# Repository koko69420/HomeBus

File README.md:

<h1 align="center">HomeBus</h1>

<p align="center">
  <strong>A deterministic, hard-wired distributed home automation platform built on 32-bit RISC-V microcontrollers, full-duplex RS-422 differential networking, centralized 24V DC power distribution, and native Home Assistant integration.</strong>
</p>

<p align="center">
  <a href="#system-architecture">Architecture</a> •
  <a href="#hierarchical-documentation">Documentation Map</a> •
  <a href="#hardware-overview">Hardware</a> •
  <a href="#protocol--firmware">Protocol & Firmware</a> •
  <a href="#repository-structure">Repository Structure</a> •
  <a href="#getting-started--toolchain">Getting Started</a>
</p>

---

## Overview & Motivation

Modern smart homes face severe reliability degradation when relying on congested 2.4 GHz wireless networks (Wi-Fi, Zigbee, Bluetooth). RF interference, wireless mesh packet dropouts, battery maintenance for wall sensors, and high-latency cloud dependencies undermine home automation dependability.

**HomeBus** solves this by delivering an industrial-grade, hard-wired residential infrastructure:
- **Full-Duplex RS-422 Differential Signaling**: Non-blocking serial communications operating at high baud rates without bus collision arbitration.
- **Centralized 24V DC Power Distribution**: Power and high-speed data are distributed over a single multi-conductor cable (CAT5e), eliminating failure-prone miniature AC-DC supplies inside cramped wall flush boxes.
- **Hardware/Logical Decoupling**: Wall switches trigger 32-bit logical device endpoints (`0xRRTTDDDD`). Physical hardware nodes (identified via 8-bit DIP switches) can be re-routed, replaced, or bridged to third-party devices (such as Tuya or Zigbee) without modifying wall switch wiring or node code.
- **Room-Level Gateway Segmentation**: Dual-transceiver gateway nodes divide the physical network into isolated room segments, insulating the central backbone from local switch traffic and safeguarding against bus-wide faults.
- **Fail-Safe Dual-Slot OTA Updates**: Permanent bootloader with ping-pong application flash partitions and automatic health verification rollbacks.

---

## System Architecture

```mermaid
flowchart TD
    subgraph Central ["Central Controller & Power Supply"]
        HA["Home Assistant Controller\n(Logical Address: 0xFFFF)\nMQTT / HomeBus Integration"]
        PSU["Central 24V 5A Industrial SMPS\n(DIN-Rail Mounted)"]
    end

    subgraph Backbone ["Backbone Bus (24V DC + RS-422 Full-Duplex)"]
        GW1["Gateway Node — Room 1\n(Dual MAX491 + EEPROM)"]
        GW2["Gateway Node — Room 2\n(Dual MAX491 + EEPROM)"]
    end

    subgraph Room1 ["Room 1 Sub-Bus (Isolated RS-422 + 24V Rail)"]
        BN1["Base Node\n(In-Wall Relays & Wall Switches)"]
        FN1["Fan Controller Node\n(AC Phase Control & Current Sense)"]
        SN1["Auxiliary Sensor Daughterboard\n(Presence / Temp / Lux)"]
    end

    subgraph Room2 ["Room 2 Sub-Bus (Isolated RS-422 + 24V Rail)"]
        BN2["Base Node\n(Multi-Channel Relay Actuator)"]
        FN2["Fan Controller Node\n(Ceiling Fan Speed)"]
    end

    HA <-->|RS-422 Backbone| GW1
    HA <-->|RS-422 Backbone| GW2
    PSU -->|24V Power Bus| GW1
    PSU -->|24V Power Bus| GW2

    GW1 <-->|Isolated Sub-Bus| BN1
    GW1 <-->|Isolated Sub-Bus| FN1
    GW1 <-->|Isolated Sub-Bus| SN1

    GW2 <-->|Isolated Sub-Bus| BN2
    GW2 <-->|Isolated Sub-Bus| FN2
```

---

## Hierarchical Documentation

The HomeBus documentation is hierarchically organized to provide deep technical detail at every layer while maintaining clean separation of concerns:

```text
README.md (Master Root)
├── Hardware/README.md (Hardware Subsystem Overview)
│   ├── base_node/README.md (In-Wall Actuator & Switch Interface)
│   ├── Gateway_node/README.md (Dual-Transceiver Room Segmentation Router)
│   ├── Fan_Controller_node/README.md (AC Phase-Angle Fan Speed Controller)
│   └── Expanders/README.md (Prototyping Adapters & Footprint Breakouts)
└── Firmware/README.md (Firmware & Protocol Specification v0.1)
```

### Direct Documentation Links

| Layer | Subsystem / Component | Key Documentation Topics | Link |
| :--- | :--- | :--- | :--- |
| **Subsystem** | **Hardware Platform** | 24V Bus power distribution, RS-422 differential signaling, SM712 surge protection, complete Bill of Materials (BOM), KiCad custom symbol & footprint libraries. | [Hardware Subsystem Overview](Hardware/README.md) |
| **Component** | **Base Node** | In-wall multi-channel relay actuator, 74HC165 switch shift register, CH32X033 TSSOP-20 pinouts (Dev vs Prod), 3D production renders, manufacturing schematics. | [Base Node README](Hardware/base_node/README.md) |
| **Component** | **Gateway Node** | Dual MAX491 transceivers, CAT24C256 I2C EEPROM routing tables, traffic monitoring LEDs, dedicated development breakout board. | [Gateway Node README](Hardware/Gateway_node/README.md) |
| **Component** | **Fan Controller Node** | H11AA1 zero-crossing detection, HCPL-3120 isolated gate drive, B2415S isolated DC-DC, KIA7N65H solid-state AC switching, active stall threshold protection. | [Fan Controller README](Hardware/Fan_Controller_node/README.md) |
| **Component** | **Expanders** | SMD prototyping daughterboards converting SOIC-14 (MAX491), SOIC-16 (74HC165), and TSSOP-20 (CH32X033) to standard 2.54 mm breadboard headers. | [Expanders README](Hardware/Expanders/README.md) |
| **Subsystem** | **Firmware & Protocol** | 32-bit Logical Device Addresses (`0xRRTTDDDD`), 8-bit Physical Node IDs, Control and Telemetry packet structures, Sensor Types, dual-slot ping-pong OTA bootloader. | [Firmware & Protocol README](Firmware/README.md) |

---

## Hardware Overview

### Base Node Production Renders

| Front View (Component Layout) | Back View (Connector & Power Rail) |
| :---: | :---: |
|  |  |

### Core Hardware Specifications
- **Processing Core**: WCH `CH32X033F8P6` (32-bit QingKe RISC-V V4C core @ 48 MHz, 62 KB Flash, 20 KB SRAM).
- **Physical Layer Transceiver**: Maxim `MAX491CSD` / `MAX491ESD` (SOP-14 full-duplex differential transceiver).
- **Bus Power Regulation**: Monolithic Power Systems `MP1584EN` (high-frequency buck converter, 24V In to 5V DC Out @ 3A).
- **Transient Protection**: ProTek `SM712` asymmetrical bidirectional TVS diode array (-7V to +12V) on all RS-422 differential pairs.
- **Input Multiplexing**: NXP / TI `74HC165D` 8-bit PISO shift register for parallel sampling of physical wall switches and the 8-bit DIP switch.
- **Visual Feedback**: Xinglight `XL-1010RGBC` (`WS2812B-1010`) addressable RGB LED for link status and diagnostics.
- **Detailed Component Records**: Complete component pricing, supplier links, and quantities are tracked in [`Hardware/BOM Home automation.xlsx`](Hardware/BOM%20Home%20automation.xlsx).

---

## Protocol & Firmware Highlights

For the full technical protocol specification, see the [Firmware & Protocol Documentation](Firmware/README.md).

### Logical vs. Physical Addressing
- **Physical Node ID (8-bit)**: Set on the hardware DIP switch (1–255). Used strictly for commissioning, OTA updates, diagnostics, and telemetry.
- **Logical Device Address (32-bit)**: Structured as `0xRRTTDDDD`:
  - `RR`: Room ID (e.g. `0x01` Living Room)
  - `TT`: Device Type (e.g. `0x01` Relay, `0x04` Fan)
  - `DDDD`: Device Unique Index
  - `0xFFFF`: Home Assistant Central Controller
- *Input nodes never transmit physical node IDs—wall switches target logical devices, allowing seamless device migration and third-party bridging.*

### Dual-Slot Failsafe OTA Bootloader
Each node partitions its 62 KB flash into a permanent bootloader (8 KB), Application Slot A (24 KB), Application Slot B (24 KB), and Non-Volatile Config (8 KB). Firmware updates are verified with 16-bit CRC before switching execution slots, with automated fallback if health confirmation is not returned.

---

## Repository Structure

```text
HomeBus/
├── Datasheets/                                # Technical datasheets for all ICs and sensors
│   ├── 7N65H.PDF                              # KEC 650V 7A Power MOSFET
│   ├── CH32X035.pdf                           # WCH RISC-V Microcontroller Series
│   ├── HCPL3120.pdf                           # Broadcom High-CMR Gate Driver
│   ├── HWCT-5A(5mA).pdf                       # AC Current Transformer
│   ├── MCP6001.pdf                            # Microchip Rail-to-Rail Op-Amp
│   ├── RGB_LED_C5349936.pdf                   # XL-1010RGBC Addressable RGB LED
│   └── vo3120.pdf                             # Vishay High-Speed Optocoupler
├── Firmware/                                  # Firmware subsystem and protocol specifications
│   ├── HomeBus Protocol Specification v0.1.docx # Upstream design document
│   └── README.md                              # Complete protocol specification & packet format guide
├── Hardware/                                  # Hardware design, schematics, and layouts
│   ├── BOM Home automation.xlsx               # Comprehensive Bill of Materials with pricing & links
│   ├── Pin Allocations.xlsx                   # MCU GPIO allocation reference (Dev vs Prod)
│   ├── README.md                              # Hardware subsystem overview & bus topology
│   ├── base_node/                             # In-wall actuator & switch node PCB (Revisions 1 to 4)
│   │   ├── Basenode_gerber/                   # Industrial fabrication Gerbers and drill maps
│   │   ├── Front_production.png               # 3D PCB front render
│   │   ├── Back_production.png                # 3D PCB back render
│   │   ├── Schematic_manufacturing.pdf        # Production schematic plot
│   │   └── README.md                          # Base Node component documentation
│   ├── Gateway_node/                          # Segmentation bridge & routing node
│   │   ├── Gateway_node_dev-board/            # Prototyping development board layout & plots
│   │   └── README.md                          # Gateway Node component documentation
│   ├── Fan_Controller_node/                   # AC phase-angle fan speed controller PCB
│   │   └── README.md                          # Fan Controller Node component documentation
│   └── Expanders/                             # SMD to 2.54mm breadboard prototyping adapters
│       └── README.md                          # Expanders component documentation
├── lib/                                       # KiCad custom symbol, footprint, and 3D libraries
│   ├── 3D_models/                             # Mechanical STEP models
│   ├── HomeBus.kicad_mod/                     # Footprint library (.kicad_mod)
│   └── HomeBus.kicad_sym                      # Schematic symbol library
├── HomeBus_Logo.png                           # Raster logo asset
├── HomeBus_Logo.svg                           # Vector logo asset
└── README.md                                  # Root documentation hub
```

---

## Getting Started & Toolchain

### Hardware Design (EDA)
- **EDA Suite**: [KiCad 7.x / 8.x](https://www.kicad.org/)
- **Opening Projects**: Double-click `.kicad_pro` inside any node directory (e.g. `Hardware/base_node/base_node_clad_v2.kicad_pro`).
- **Libraries**: All custom components are pre-configured in project-relative paths pointing to `lib/HomeBus.kicad_sym` and `lib/HomeBus.kicad_mod/`.

### Firmware Development & Debugging
- **Core Architecture**: QingKe 32-bit RISC-V V4C (`rv32imac`).
- **Toolchain**: `riscv-none-elf-gcc` / MounRiver Studio / OpenOCD for WCH.
- **Hardware Debugger**: [WCH-LinkE](https://www.wch-ic.com/products/WCH-Link.html) programmer/debugger connected via 1-wire SWD (`SWDIO`, `SWCLK`, `GND`, `3V3`).

---

## License & Authorship

All hardware designs, schematics, PCB artwork, and protocol specifications are authored by **Kaustubh** (`koko69420`). All rights reserved.

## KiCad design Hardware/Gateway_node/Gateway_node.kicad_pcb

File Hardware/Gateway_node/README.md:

# HomeBus Gateway Node

The **HomeBus Gateway Node** serves as the vital routing bridge, segmentation barrier, and protocol proxy between the central HomeBus **Trunk Backbone Bus** and individual **Room Sub-Buses**.

By dividing the physical automation topology into isolated room-level segments, the Gateway prevents local switch bounces, encoder streams, and internal room traffic from congesting the primary backbone while safeguarding against bus-wide failures.

---

## Visual Previews

### Development Board Copper Layout
The development breakout board provides full access to debugging interfaces, bus headers, and test points:

| Gateway Node Dev Board (Top Copper) |
| :---: |
|  |

---

## System Architecture & Routing Principle

```mermaid
flowchart TD
    subgraph Backbone ["Backbone Trunk (24V + RS-422)"]
        HA["Home Assistant Controller\n(Address: 0xFFFF)"] <--> TRUNK_BUS["Trunk RS-422 Differential Pair"]
    end

    subgraph GatewayNode ["HomeBus Gateway Node"]
        TRUNK_XCVR["Trunk MAX491\nTransceiver"]
        MCU["WCH CH32X033F8P6\n(32-bit QingKe RISC-V)"]
        ROOM_XCVR["Room MAX491\nTransceiver"]
        EEPROM["AT24C256 / CAT24C256\n(256 Kbit I2C EEPROM)"]
        LED_TRUNK["Traffic LED Trunk\n(Activity Monitor)"]
        LED_ROOM["Traffic LED Room\n(Activity Monitor)"]
        DIP["8-Bit DIP Switch\n(Gateway Node ID)"]

        TRUNK_BUS <--> TRUNK_XCVR
        TRUNK_XCVR <-->|UART Trunk TX/RX| MCU
        MCU <-->|UART Room TX/RX| ROOM_XCVR
        MCU <-->|I2C SDA/SCL| EEPROM
        MCU --> LED_TRUNK
        MCU --> LED_ROOM
        DIP -->|74HC165 Shift Reg| MCU
    end

    subgraph RoomBus ["Room Sub-Bus (Isolated RS-422)"]
        ROOM_XCVR <--> ROOM_DEVS["Base Nodes / Fan Nodes / Sensor Nodes"]
    end
```

### Gateway Functional Roles
1. **Packet Filtering & Forwarding**:
   - Packets addressed to devices located within the room are routed locally and never leak to the backbone.
   - External commands from Home Assistant (`0xFFFF`) targeting room devices (`0xRRTTDDDD`) are recognized by the Gateway's Room ID prefix (`RR`) and forwarded inward.
   - Sensor telemetry packets from room nodes are forwarded outbound to Home Assistant.
2. **Device Address Resolution & Caching**:
   - The Gateway maintains a local device table in onboard 256-Kbit EEPROM (`AT24C256`).
   - If a logical device (e.g. `0x02030005`) maps to a third-party Tuya smart device or secondary wireless gateway, the Gateway handles the protocol bridge transparently.
3. **OTA Firmware Proxy**:
   - Buffers and relays firmware update blocks destined for individual room nodes, ensuring reliable transmission over point-to-point RS-422 links.

---

## Key Hardware Components

| Component | Part / Package | Subsystem | Description & Function |
| :--- | :--- | :--- | :--- |
| **MCU** | WCH `CH32X033F8P6` (TSSOP-20) | Core Processing | 48 MHz 32-bit RISC-V QingKe V4C core. Manages dual UARTs, packet routing, CRC verification, and routing table lookup. |
| **Trunk Transceiver** | Maxim `MAX491E` (SOP-14) | Backbone Interface | Full-duplex RS-422 transceiver interfacing the high-speed central backbone network. |
| **Room Transceiver** | Maxim `MAX491E` (SOP-14) | Room Sub-Bus | Dedicated full-duplex RS-422 transceiver driving the isolated room sub-bus. |
| **Non-Volatile Memory**| Microchip `AT24C256C` / `CAT24C256` (SOIC-8) | Routing Storage | 256-Kbit (32 KByte) I2C EEPROM. Stores routing tables, device mapping registers, and offline fallback states. |
| **Surge Protection** | ProTek `SM712` (SOT-23) | Bus Protection | Dual asymmetrical TVS diode arrays (-7V to +12V) on both Trunk and Room differential lines. |
| **Shift Register** | TI/NXP `74HC165D` (SOP-16) | Input Multiplexer | Parallel-to-serial shift register reading the 8-position hardware Node ID DIP switch. |
| **Traffic Indicators**| Discrete SMD LEDs + Current Limiters | Diagnostics | Independent status LEDs indicating real-time packet activity on Trunk and Room buses. |
| **Status LED** | Xinglight `XL-1010RGBC` (`WS2812B`) | System Status | Addressable RGB indicator showing boot state, bus lock, error conditions, and sync status. |

---

## Pin Allocation Table

The Gateway Node uses the 20-pin `CH32X033F8P6` to manage dual transceivers, EEPROM, and traffic indication:

| Pin # | MCU Pin | Production Function | Development Function | Net / Description |
| :---: | :---: | :---: | :---: | :--- |
| **1** | PA0 / PC3 | `DNC` | `Boot Switch` | Do Not Connect in Production; Bootloader Entry Switch in Development |
| **2** | PA1 / PC4 | `Room MAX491 DI` | `Room MAX491 DI` | RS-422 Driver Input (MCU UART TX to Room Sub-Bus) |
| **3** | PA2 / PC2 | `Room MAX491 RO` | `Room MAX491 RO` | RS-422 Receiver Output (Room Sub-Bus RX to MCU) |
| **4** | NRST | `RST` | `RST` | Hardware Reset line (active low, pulled high) |
| **5** | PB0 / PC0 | `HC165 Q7` | `HC165 Q7` | 74HC165 Shift Register Serial Data Out (Node ID data) |
| **6** | PB1 | `Neopixel` | `Neopixel` | Single-wire NRZ serial data stream to WS2812B RGB LED |
| **7** | VSS | `GND` | `GND` | System Ground (0V reference) |
| **8** | PB2 / PC6 | `DNC` | `SWDIO` | Do Not Connect in Production; WCH SWD Debug Data in Development |
| **9** | VDD | `VDD` | `VDD` | Logic Supply Rail (+5V / +3.3V) |
| **10** | PB3 / PC8 | `DNC` | `SWD RX` | Do Not Connect in Production; Debug UART RX in Development |
| **11** | PB6 | `I2C SDA` | `I2C SDA` | I2C Serial Data line to CAT24C256 EEPROM |
| **12** | PB7 | `I2C SCL` | `I2C SCL` | I2C Serial Clock line to CAT24C256 EEPROM |
| **13** | PB4 / PC5 | `Traffic Led Trunk` | `Traffic Led Trunk` | Activity LED driver for Trunk Backbone packet transmission |
| **14** | PB5 | `HC165 PL_` | `HC165 PL_` | 74HC165 Shift Register Parallel Load (active low) |
| **15** | PB8 | `HC165 CP` | `HC165 CP` | 74HC165 Shift Register Clock Pulse |
| **16** | PB10 | `MAX491 DI` | `MAX491 DI` | Trunk RS-422 Driver Input (MCU UART TX to Backbone Bus) |
| **17** | PB11 | `MAX491 RO` | `MAX491 RO` | Trunk RS-422 Receiver Output (Backbone Bus RX to MCU) |
| **18** | PB9 / PC7 | `DNC` | `SWCLK` | Do Not Connect in Production; WCH SWD Clock in Development |
| **19** | PA3 / PC1 | `Traffic Led Room` | `Traffic Led Room` | Activity LED driver for Room Sub-Bus packet transmission |
| **20** | PA4 / PC9 | `DNC` | `SWD TX` | Do Not Connect in Production; Debug UART TX in Development |

---

## Development Board Breakout

The repository includes a dedicated breakout board under [`Gateway_node_dev-board/`](Gateway_node_dev-board/):
- **Features**:
  - Full breakout headers for all 20 MCU pins, allowing logic analyzer probing and rapid breadboard interfacing.
  - Onboard tactile buttons for `Boot` and `Reset`.
  - Dual MAX491 screw terminals and test pin sockets.
  - Dedicated WCH-LinkE programming header (SWDIO, SWCLK, 3.3V, GND, TX, RX).
- **Fabrication Plots**:
  - Top Copper: [`Gateway_node_dev-board-F_Cu.pdf`](Gateway_node_dev-board/Gateway_node_dev-board-F_Cu.pdf)
  - Bottom Copper: [`Gateway_node_dev-board-B_Cu.pdf`](Gateway_node_dev-board/Gateway_node_dev-board-B_Cu.pdf)
  - Outline: [`Gateway_node_dev-board-Edge_Cuts.pdf`](Gateway_node_dev-board/Gateway_node_dev-board-Edge_Cuts.pdf)

---

## Navigation

- [← Hardware Subsystem Overview](../README.md)
- [↑ HomeBus Root Documentation](../../README.md)
- [Base Node Documentation →](../base_node/README.md)
- [Fan Controller Node Documentation →](../Fan_Controller_node/README.md)
- [Expander Daughterboards Documentation →](../Expanders/README.md)
- [Firmware & Protocol Specification →](../../Firmware/README.md)

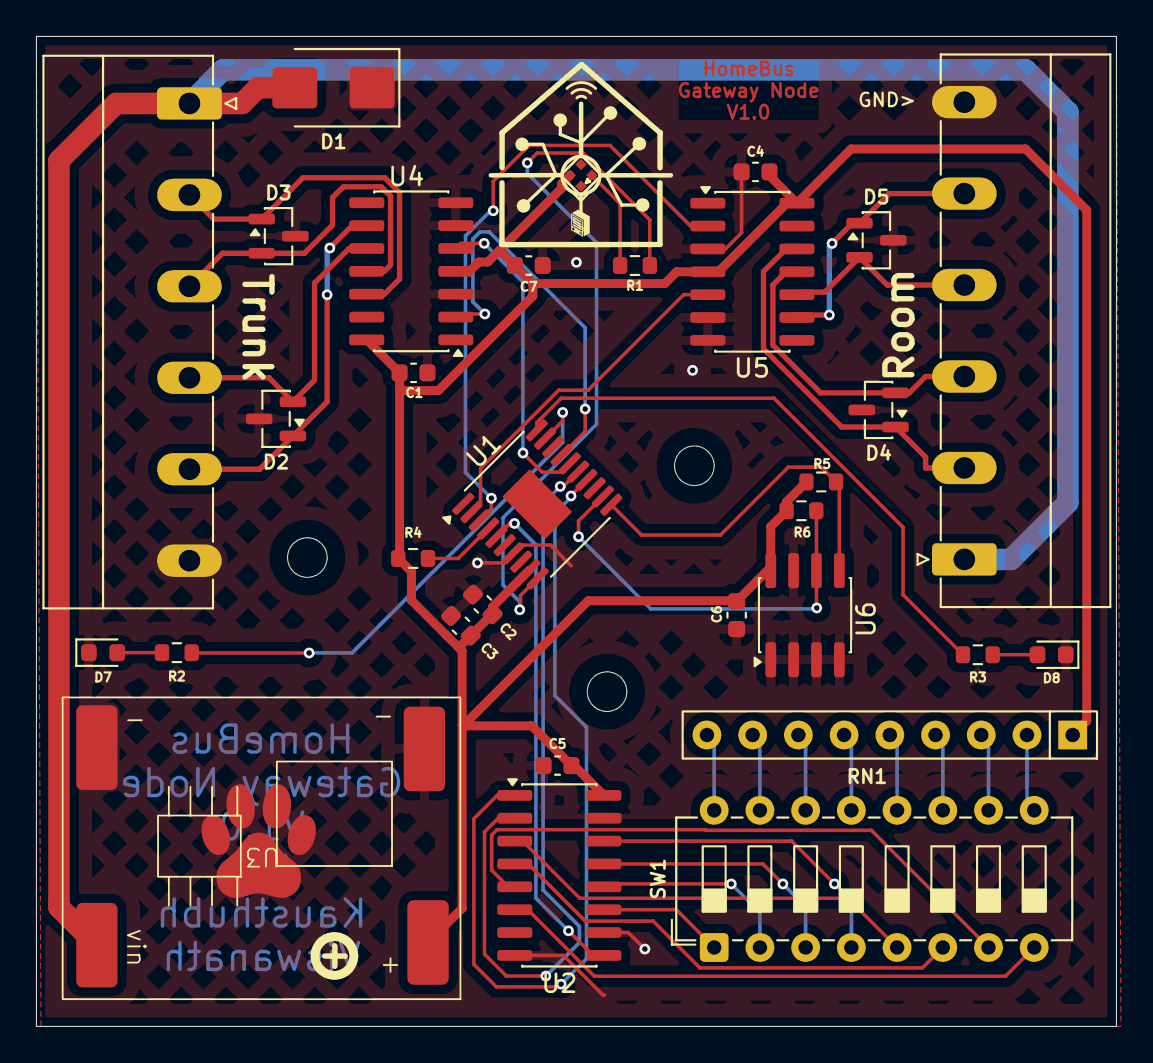
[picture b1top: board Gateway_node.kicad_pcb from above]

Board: 2 copper layers, 60.0 x 55.0 mm, 32 parts (1 on the bottom side), 43 nets.

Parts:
C1, C2, C4, C5, C6, C7: 100nF; C_0603_1608Metric
C3: 10uF; C_0603_1608Metric
D1: D_TVS; D_SMB
D2, D3, D4, D5: SM712_SOT23; SOT-23
D6: WS2812B; XINGLIGHT-XL-1010RGBC-WS2812B
D7, D8: LED; LED_0603_1608Metric
J1: RS-422 Room; PhoenixContact_MC_1,5_6-G-5.08_1x06_P5.08mm_Horizontal
J2: RS-422 Trunk; PhoenixContact_MC_1,5_6-G-5.08_1x06_P5.08mm_Horizontal
Lg2: OSHW-Logo_5.7x6mm_SilkScreen
R1: 330Ω; R_0603_1608Metric
R2, R3: 10kΩ; R_0603_1608Metric
R4: 10KΩ; R_0603_1608Metric
R5, R6: 4.7kΩ; R_0603_1608Metric
RN1: 10KΩ; R_Array_SIP9
SW1: SW_DIP_x08; SW_DIP_SPSTx08_Slide_6.7x21.88mm_W7.62mm_P2.54mm_LowProfile
U1: CH32X033F8P6; TSSOP-20-1EP_4.4x6.5mm_P0.65mm_EP2.15x3.35mm
U2: 74HC165; SOIC-16_3.9x9.9mm_P1.27mm
U3: MP1584 Module
U4, U5: MAX491E; SOIC-14_3.9x8.7mm_P1.27mm
U6: AT24C256C-SSHL; SOIC-8_3.9x4.9mm_P1.27mm

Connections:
+5V: C1.2, C2.1, C3.1, C4.2, C5.1, C6.1, C7.2, D6.1 (VDD), R4.1, R5.2, R6.2, RN1.1 (common), U1.9 (Vdd), U2.16 (VCC), U3.3 (VOUT), U4.4 (DE), U4.14 (VCC), U5.4 (DE), U5.14 (VCC), U6.8 (VCC)
+24V: D1.2 (A2), J1.1, J2.1, U3.1 (VIN)
GND: C1.1, C2.2, C3.2, C4.1, C5.2, C6.2, C7.1, D1.1 (A1), D2.3 (common), D3.3 (common), D4.3 (common), D5.3 (common), D6.3 (VSS), D7.1 (K), D8.1 (K), J1.6, J2.6, U1.7 (GND), U2.8 (GND), U2.10 (DS), U2.15 (~CE), U3.2 (GND), U3.4 (GND), U4.3 (~RE), U4.6 (GND), U4.7 (GND), U5.3 (~RE), U5.6 (GND), U5.7 (GND), U6.1 (A0), U6.2 (A1), U6.3 (A2), U6.4 (GND), U6.7 (WP)
unnamed: D2.1 (A1), J2.5, U4.9 (Y)
unnamed: D2.2 (A2), J2.4, U4.10 (Z)
unnamed: D3.1 (A1), J2.2, U4.12 (A)
unnamed: D3.2 (A2), J2.3, U4.11 (B)
unnamed: D4.1 (A1), J1.2, U5.12 (A)
unnamed: D4.2 (A2), J1.3, U5.11 (B)
unnamed: D5.1 (A1), J1.5, U5.9 (Y)
unnamed: D5.2 (A2), J1.4, U5.10 (Z)
unnamed: D6.4 (DIN), R1.2
unnamed: D7.2 (A), R2.1
unnamed: D8.2 (A), R3.2
unnamed: RN1.2 (R1), SW1.9
unnamed: RN1.3 (R2), SW1.10
unnamed: RN1.4 (R3), SW1.11
unnamed: RN1.5 (R4), SW1.12
unnamed: RN1.6 (R5), SW1.13
unnamed: RN1.7 (R6), SW1.14
unnamed: RN1.8 (R7), SW1.15
unnamed: RN1.9 (R8), SW1.16
unnamed: U1.14 (PA0/A0), U2.1 (~PL)
unnamed: U1.15 (PA1/A1), U2.2 (CP)
unnamed: U1.16 (PA2/TX2), U4.5 (DI)
unnamed: U1.17 (PA3/RX2), U4.2 (RO)
unnamed: R2.2, U1.19 (PA4)
unnamed: R3.1, U1.20 (PA5)
unnamed: U1.2 (PA7/MOSI), U5.5 (DI)
unnamed: R1.1, U1.10 (PA9)
unnamed: R6.1, U1.12 (PA10/TX1/SCK), U6.6 (SCL)
unnamed: R5.1, U1.11 (PA11/RX1/SDA), U6.5 (SDA)
unnamed: U1.3 (PB1/A9), U5.2 (RO)
unnamed: R4.2, U1.4 (PB7/RST)
unnamed: U1.5 (PC16), U2.9 (Q7)
unnamed: SW1.1, U2.11 (D0)
unnamed: SW1.2, U2.12 (D1)
unnamed: SW1.3, U2.13 (D2)
unnamed: SW1.4, U2.14 (D3)
unnamed: SW1.5, U2.3 (D4)
unnamed: SW1.6, U2.4 (D5)
unnamed: SW1.7, U2.5 (D6)
unnamed: SW1.8, U2.6 (D7)

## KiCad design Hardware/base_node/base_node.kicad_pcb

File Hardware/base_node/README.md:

# HomeBus Base Node

The **HomeBus Base Node** is the primary in-wall actuator and sensor module in the HomeBus distributed automation network. Designed to fit into standard residential switch flush boxes behind wall plates, it interfaces physical toggle switches and rotary encoders with the HomeBus RS-422 serial bus while driving external relay modules to switch lights, appliances, and inductive loads.

---

## Visual Previews

### 3D Production Renders
| Front View (Component Side) | Back View (Connector Side) |
| :---: | :---: |
|  |  |

### Manufacturing Schematic

---

## Hardware Architecture

```mermaid
flowchart LR
    subgraph Power ["Power Subsystem"]
        BUS_IN["24V DC Bus Rail"] --> BUCK["MP1584EN Buck Converter\n(24V -> 5V DC @ 3A)"]
        BUCK --> VDD["5V Logic Rail"]
    end

    subgraph BusInterface ["RS-422 Interface"]
        RS422["XY2500 6-Pin Bus Header\n(24V, GND, TX±, RX±)"]
        TVS["SM712 TVS Array\n(-7V to +12V Protection)"]
        XCVR["MAX491 Transceiver\n(Full-Duplex RS-422)"]
        RS422 <--> TVS <--> XCVR
    end

    subgraph Processing ["Core MCU"]
        MCU["WCH CH32X033F8P6\n(32-bit QingKe RISC-V @ 48 MHz)"]
    end

    subgraph Inputs ["Input Subsystem"]
        DIP["8-Bit DIP Switch\n(Hardware Node ID)"]
        WALL["External Wall Switches /\nRotary Encoders (JST-PH)"]
        SR["74HC165D Shift Register\n(8-bit PISO Shift Register)"]
        DIP --> SR
        WALL --> SR
    end

    subgraph Indicators ["Visual Feedback"]
        LED["WS2812B-1010 Addressable RGB LED\n(Status / Diagnostics)"]
    end

    subgraph Outputs ["Actuator Expansion"]
        EXP["IDC 2x5 Expansion Header\n(Relay Control GPIOC 1-5, 8, 9)"]
    end

    XCVR <-->|UART DI / RO| MCU
    SR -->|Serial Q7, PL_, CP| MCU
    MCU -->|Serial WS2812 Data| LED
    MCU -->|GPIO Outputs| EXP
    VDD --> MCU
    VDD --> XCVR
    VDD --> SR
```

---

## Key Hardware Components

| Subsystem | Component | Package | Function / Rationale |
| :--- | :--- | :--- | :--- |
| **Microcontroller** | WCH `CH32X033F8P6` | TSSOP-20 | QingKe 32-bit RISC-V V4C core @ 48 MHz, 62 KB Flash, 20 KB SRAM. Handles RS-422 protocol stack, switch debouncing, and relay actuation. |
| **Transceiver** | Maxim `MAX491CSD` / `MAX491ESD` | SOP-14 | High-speed, full-duplex RS-422/RS-485 differential transceiver. Allows simultaneous transmit and receive with no collision backoff. |
| **Input Multiplexer** | NXP / TI `74HC165D` | SOP-16 | 8-bit Parallel-In Serial-Out (PISO) shift register. Samples the 8-bit DIP switch and wall inputs using only 3 MCU pins (`PL_`, `CP`, `Q7`). |
| **Power Converter** | Monolithic Power `MP1584EN` | Modular Module | 3A high-frequency step-down switching buck regulator module converting centralized 24V bus power to regulated 5V system logic. |
| **Surge Protection** | ProTek `SM712` / `PSM712` | SOT-23 | Asymmetrical bidirectional TVS diode array (-7V to +12V) specifically engineered for RS-422 lines against ESD, EFT, and power transients. |
| **Status Indicator** | Xinglight `XL-1010RGBC` (`WS2812B-1010`) | SMD-1010 (1.0x1.0mm) | Ultra-compact single-wire addressable RGB LED for status indication, network link health, and commissioning feedback. |
| **Hardware ID** | 8-Position SPST DIP Switch | 2.54mm Pitch Slide | Configures physical Node ID (1–255) for commissioning, telemetry, and OTA management. |

---

## Pin Allocation Table

The Base Node assigns the 20 pins of the `CH32X033F8P6` as follows, differentiating between **Development** mode (SWD debug available) and **Production** mode (SWD pins repurposed for actuator GPIOs):

| Pin # | MCU Pin | Production Function | Development Function | Net / Description |
| :---: | :---: | :---: | :---: | :--- |
| **1** | PA0 / PC3 | `GPIOC 3` | `Boot Switch` | Actuator Output 3 in Production; Bootloader entry trigger in Development |
| **2** | PA1 / PC4 | `GPIOC 4` | `GPIOC 4` | Actuator Output 4 / Relay drive line |
| **3** | PA2 / PC2 | `GPIOC 2` | `GPIOC 2` | Actuator Output 2 / Relay drive line |
| **4** | NRST | `RST` | `RST` | Hardware Reset line (active low, with pull-up) |
| **5** | PB0 / PC0 | `HC165 Q7` | `HC165 Q7` | Shift Register Serial Data Out (MISO stream to MCU) |
| **6** | PB1 | `Neopixel` | `Neopixel` | High-speed single-wire NRZ serial data stream to WS2812B LED |
| **7** | VSS | `GND` | `GND` | System Ground (0V reference) |
| **8** | PB2 / PC6 | `GPIOC 6` | `SWDIO` | Actuator Output 6 in Production; WCH SWD Debug Data in Development |
| **9** | VDD | `VDD` | `VDD` | Logic Supply Rail (+5V DC from MP1584EN) |
| **10** | PB3 / PC8 | `GPIOC 8` | `SWD RX` | Actuator Output 8 in Production; Debug UART RX in Development |
| **11** | PB6 | `I2C SDA` | `I2C SDA` | I2C Serial Data line for auxiliary sensor daughterboards |
| **12** | PB7 | `I2C SCL` | `I2C SCL` | I2C Serial Clock line for auxiliary sensor daughterboards |
| **13** | PB4 / PC5 | `GPIOC 5` | `GPIOC 5` | Actuator Output 5 / Relay drive line |
| **14** | PB5 | `HC165 PL_` | `HC165 PL_` | 74HC165 Asynchronous Parallel Load (active low) |
| **15** | PB8 | `HC165 CP` | `HC165 CP` | 74HC165 Shift Register Clock Pulse |
| **16** | PB10 | `MAX491 DI` | `MAX491 DI` | RS-422 Driver Input (MCU UART TX to RS-422 differential bus) |
| **17** | PB11 | `MAX491 RO` | `MAX491 RO` | RS-422 Receiver Output (RS-422 differential bus to MCU UART RX) |
| **18** | PB9 / PC7 | `GPIOC 7` | `SWCLK` | Actuator Output 7 in Production; WCH SWD Clock in Development |
| **19** | PA3 / PC1 | `GPIOC 1` | `GPIOC 1` | Actuator Output 1 / Relay drive line |
| **20** | PA4 / PC9 | `GPIOC 9` | `SWD TX` | Actuator Output 9 in Production; Debug UART TX in Development |

---

## Revision History

1. **`base_node` (v1.0)**: Initial prototype layout. Used orthogonal 45° routing and tested basic connectivity between the CH32X033 and MAX491.
2. **`base_node-rounded` (v1.1)**: Experimental PCB layout with circular/curved track fillets using KiCad round-tracks plugin for aesthetic evaluation and high-speed trace continuity.
3. **`base_node_clad` (v1.2)**: Added continuous solid copper pour cladding across top and bottom layers, significantly reducing ground impedance and improving EMI containment in high-noise AC environments.
4. **`base_node_clad_v2` (v2.0 - Production)**:
   - Optimized high-voltage isolation creepage and clearance distances between mains-connected lines and low-voltage logic.
   - Refined component clearances for compact hand-soldering and reflow stenciling.
   - Added reinforced thermal pads and teardrop transitions on signal vias.
   - Verified Gerber generation ready for industrial fabrication under [`Basenode_gerber/`](Basenode_gerber/).

---

## Manufacturing & Assembly

- **Gerber Files**: Ready-to-manufacture archives are stored in [`Basenode_gerber/base_node.zip`](Basenode_gerber/base_node.zip).
- **PCB Fabrication Parameters**:
  - Layers: 2-layer FR-4
  - Board Thickness: 1.6 mm
  - Copper Weight: 1 oz (35 µm)
  - Surface Finish: HASL Lead-Free / ENIG recommended
  - Minimum Trace / Space: 0.2 mm / 0.2 mm
  - Solder Mask: Blue / Matte Black
  - Silkscreen: White
- **Fabrication Plots**:
  - Top Copper: [`base_node_clad_v2-F_Cu.pdf`](base_node_clad_v2-F_Cu.pdf)
  - Bottom Copper: [`base_node_clad_v2-B_Cu.pdf`](base_node_clad_v2-B_Cu.pdf)
  - Edge Cuts / Outline: [`base_node_clad_v2-Edge_Cuts.pdf`](base_node_clad_v2-Edge_Cuts.pdf)

---

## Navigation

- [← Hardware Subsystem Overview](../README.md)
- [↑ HomeBus Root Documentation](../../README.md)
- [Gateway Node Documentation →](../Gateway_node/README.md)
- [Fan Controller Node Documentation →](../Fan_Controller_node/README.md)
- [Expander Daughterboards Documentation →](../Expanders/README.md)
- [Firmware & Protocol Specification →](../../Firmware/README.md)

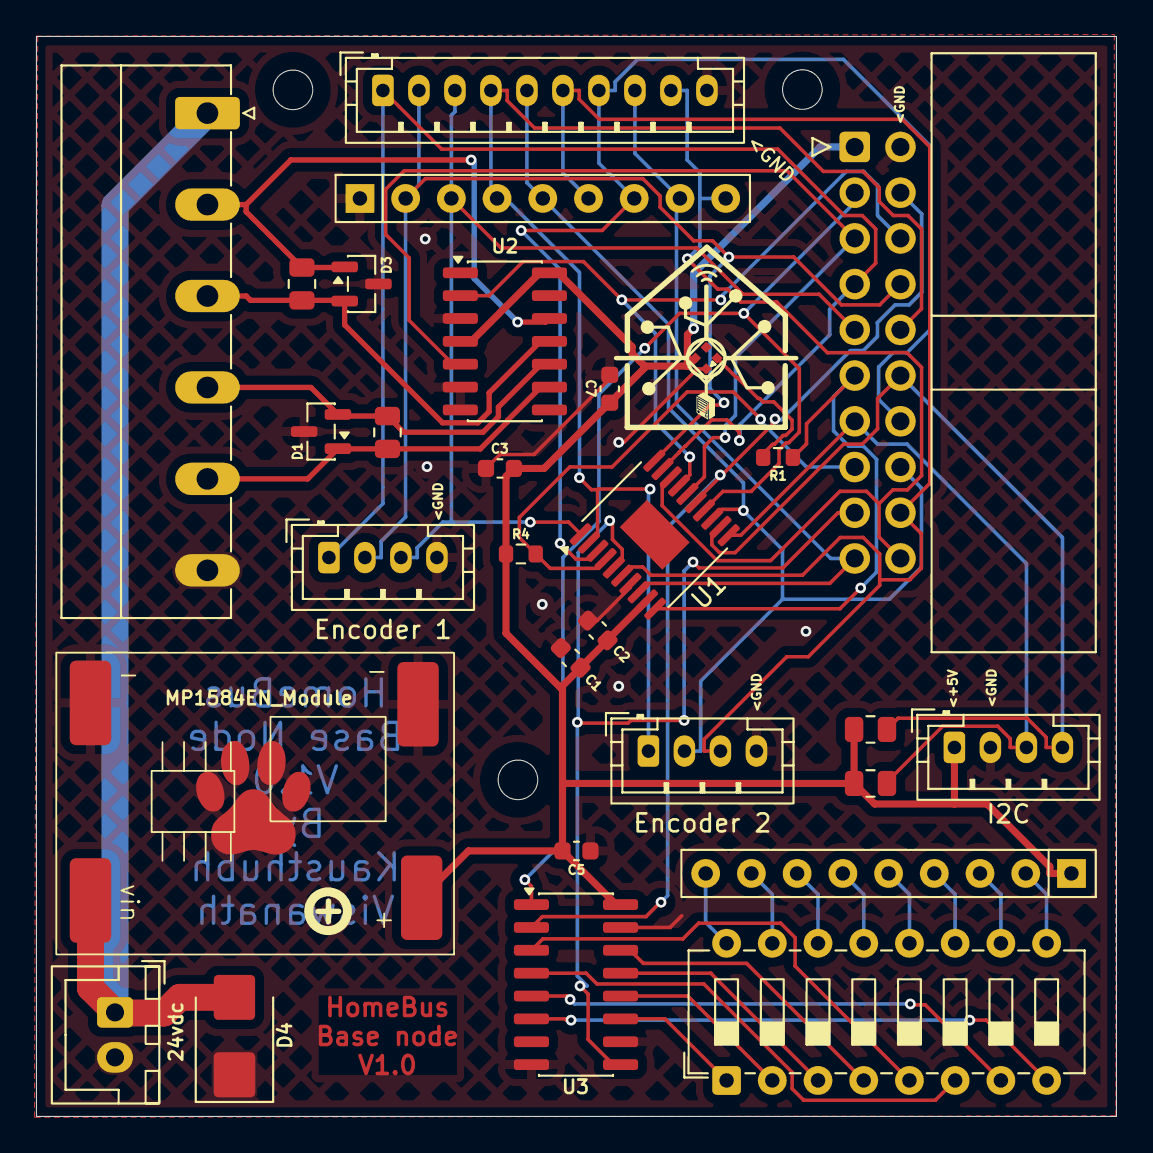
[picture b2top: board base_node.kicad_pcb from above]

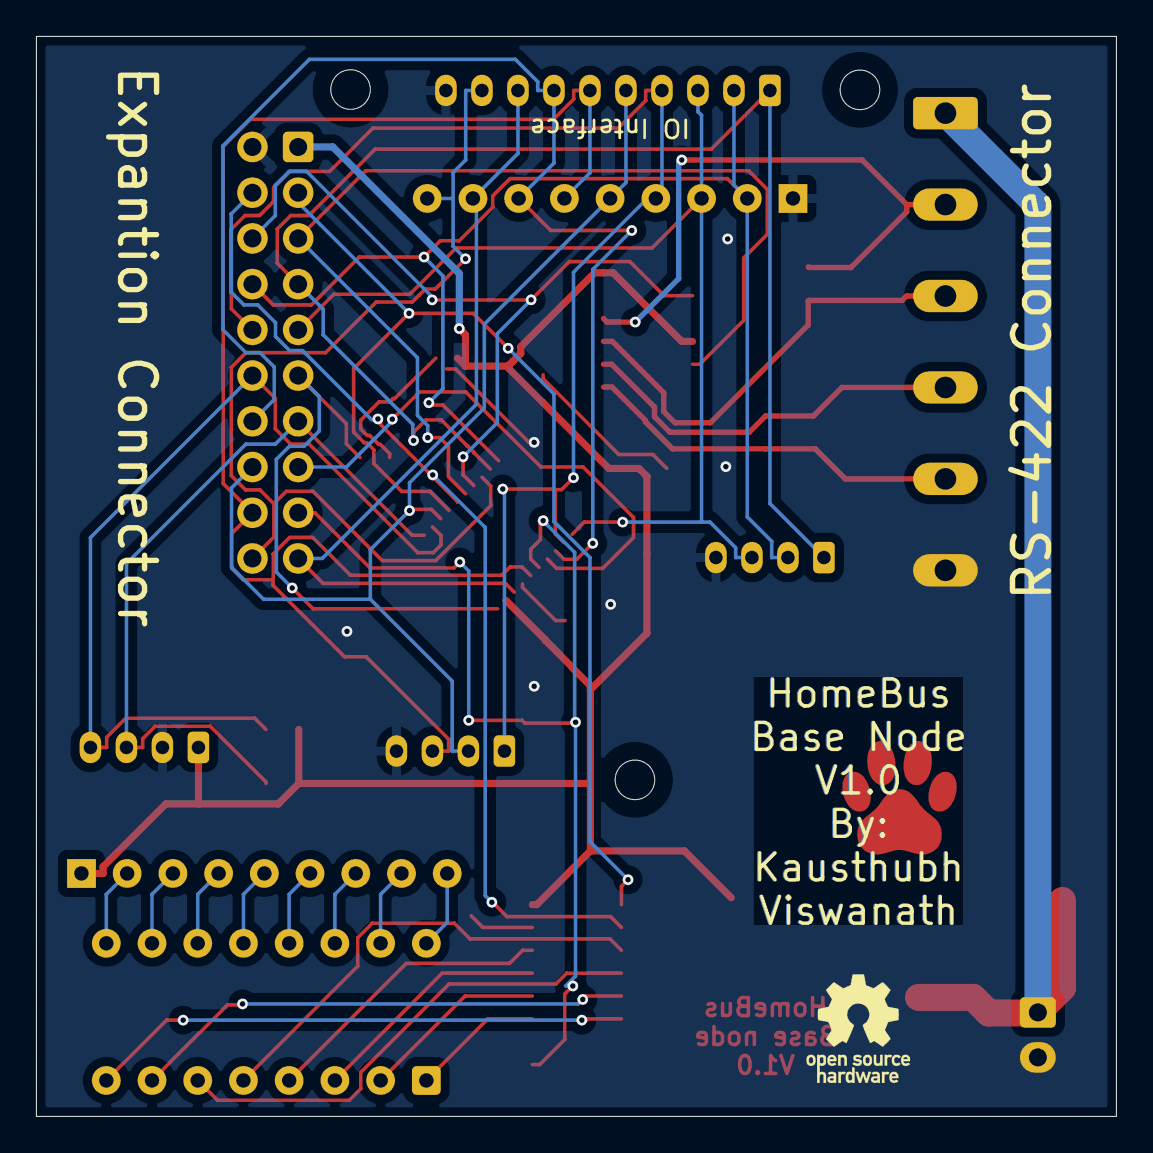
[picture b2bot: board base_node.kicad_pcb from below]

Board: 2 copper layers, 60.0 x 60.0 mm, 34 parts (4 on the bottom side), 42 nets.

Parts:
C1, C3, C5, C7: 100nF; C_0603_1608Metric
C2: 10uF; C_0603_1608Metric
D1, D3: SM712_SOT23; SOT-23
D2: WS2812B; XINGLIGHT-XL-1010RGBC-WS2812B
D4: SMBJ26A; D_SMB
J1: IO Interface; JST_PH_B10B-PH-K_1x10_P2.00mm_Vertical
J2: RS-422 Connector; PhoenixContact_MC_1,5_6-G-5.08_1x06_P5.08mm_Horizontal
J3: Expantion Connector; IDC-Header_2x10_P2.54mm_Horizontal
J4: I2C; JST_PH_B4B-PH-K_1x04_P2.00mm_Vertical
J5: 24vdc; JST_XH_B2B-XH-A_1x02_P2.50mm_Vertical
J6: Encoder 1; JST_PH_B4B-PH-K_1x04_P2.00mm_Vertical
J7: Encoder 2; JST_PH_B4B-PH-K_1x04_P2.00mm_Vertical
Lg1: HomeBus_LOGO
Lg2: OSHW-Logo_5.7x6mm_SilkScreen
Mount1, Mount2, Mount3: MountingHole_2.2mm_M2
R1: 330Ω; R_0603_1608Metric
R4: 10KΩ; R_0603_1608Metric
R5, R6: 120Ω; R_0805_2012Metric
R7, R8: 4.7kΩ; R_0805_2012Metric
RN1, RN2: 10KΩ; R_Array_SIP9
SW1: SW_DIP_x08; SW_DIP_SPSTx08_Slide_6.7x21.88mm_W7.62mm_P2.54mm_LowProfile
U1: CH32X033F8P6; TSSOP-20-1EP_4.4x6.5mm_P0.65mm_EP2.15x3.35mm
U2: MAX491E; SOIC-14_3.9x8.7mm_P1.27mm
U3: 74HC165; SOIC-16_3.9x9.9mm_P1.27mm
U4: MP1584EN_Module; MP1584 Module

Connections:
+5V: C1.1, C2.1, C3.2, C5.1, C7.2, D2.1 (VDD), J3.1, J4.1, R4.1, R7.1, R8.1, RN1.1 (common), U1.9 (Vdd), U2.4 (DE), U2.14 (VCC), U3.16 (VCC), U4.3 (VOUT)
/+24V: D4.2 (A2), J2.1, J5.1, U4.1 (VIN)
/RX+: D1.1 (A1), J2.5, R6.1, U2.9 (Y)
/RX-: D1.2 (A2), J2.4, R6.2, U2.10 (Z)
/SCL: J3.12, J4.4, R8.2, U1.12 (PA10/TX1/SCK)
/SDA: J3.13, J4.3, R7.2, U1.11 (PA11/RX1/SDA)
/TX+: D3.1 (A1), J2.2, R5.1, U2.12 (A)
/TX-: D3.2 (A2), J2.3, R5.2, U2.11 (B)
GND: C1.2, C2.2, C3.1, C5.2, C7.1, D1.3 (common), D2.3 (VSS), D3.3 (common), D4.1 (A1), J1.10, J2.6, J3.2, J4.2, J5.2, J6.4, J7.4, RN2.1 (common), U1.7 (GND), U2.3 (~RE), U2.6 (GND), U2.7 (GND), U3.8 (GND), U3.10 (DS), U3.15 (~CE), U4.2 (GND), U4.4 (GND)
unnamed: D2.4 (DIN), R1.2
unnamed: J1.1, J3.7, J6.1, U1.19 (PA4)
unnamed: J1.2, J3.8, J6.2, RN2.2 (R1), U1.20 (PA5)
unnamed: J1.3, J3.9, J6.3, RN2.3 (R2), U1.1 (PA6/MSIO)
unnamed: J1.4, J3.10, J7.1, RN2.4 (R3), U1.2 (PA7/MOSI)
unnamed: J1.5, J3.16, J7.2, RN2.5 (R4), U1.13 (PC3)
unnamed: J1.6, J3.18, J7.3, RN2.6 (R5), U1.6 (PC17)
unnamed: J1.7, J3.14, RN2.7 (R6), U1.3 (PB1/A9)
unnamed: J1.8, J3.19, RN2.8 (R7), U1.8 (USART3_TC)
unnamed: J1.9, J3.20, RN2.9 (R8), U1.18 (USART3_RX)
unnamed: J3.3, U1.14 (PA0/A0), U3.1 (~PL)
unnamed: J3.4, U1.15 (PA1/A1), U3.2 (CP)
unnamed: J3.5, U1.16 (PA2/TX2), U2.5 (DI)
unnamed: J3.6, U1.17 (PA3/RX2), U2.2 (RO)
unnamed: J3.11, R1.1, U1.10 (PA9)
unnamed: J3.15, R4.2, U1.4 (PB7/RST)
unnamed: J3.17, U1.5 (PC16), U3.9 (Q7)
unnamed: RN1.2 (R1), SW1.9
unnamed: RN1.3 (R2), SW1.10
unnamed: RN1.4 (R3), SW1.11
unnamed: RN1.5 (R4), SW1.12
unnamed: RN1.6 (R5), SW1.13
unnamed: RN1.7 (R6), SW1.14
unnamed: RN1.8 (R7), SW1.15
unnamed: RN1.9 (R8), SW1.16
unnamed: SW1.1, U3.11 (D0)
unnamed: SW1.2, U3.12 (D1)
unnamed: SW1.3, U3.13 (D2)
unnamed: SW1.4, U3.14 (D3)
unnamed: SW1.5, U3.3 (D4)
unnamed: SW1.6, U3.4 (D5)
unnamed: SW1.7, U3.5 (D6)
unnamed: SW1.8, U3.6 (D7)

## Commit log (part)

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2026-06-21 Initial HomeBus commit
2026-06-21 Remove KiCad temporary files
